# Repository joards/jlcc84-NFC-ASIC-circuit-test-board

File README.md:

# jlcc84-NFC-ASIC-circuit-test-board
PCB created to test custom NFC ASIC in master project.

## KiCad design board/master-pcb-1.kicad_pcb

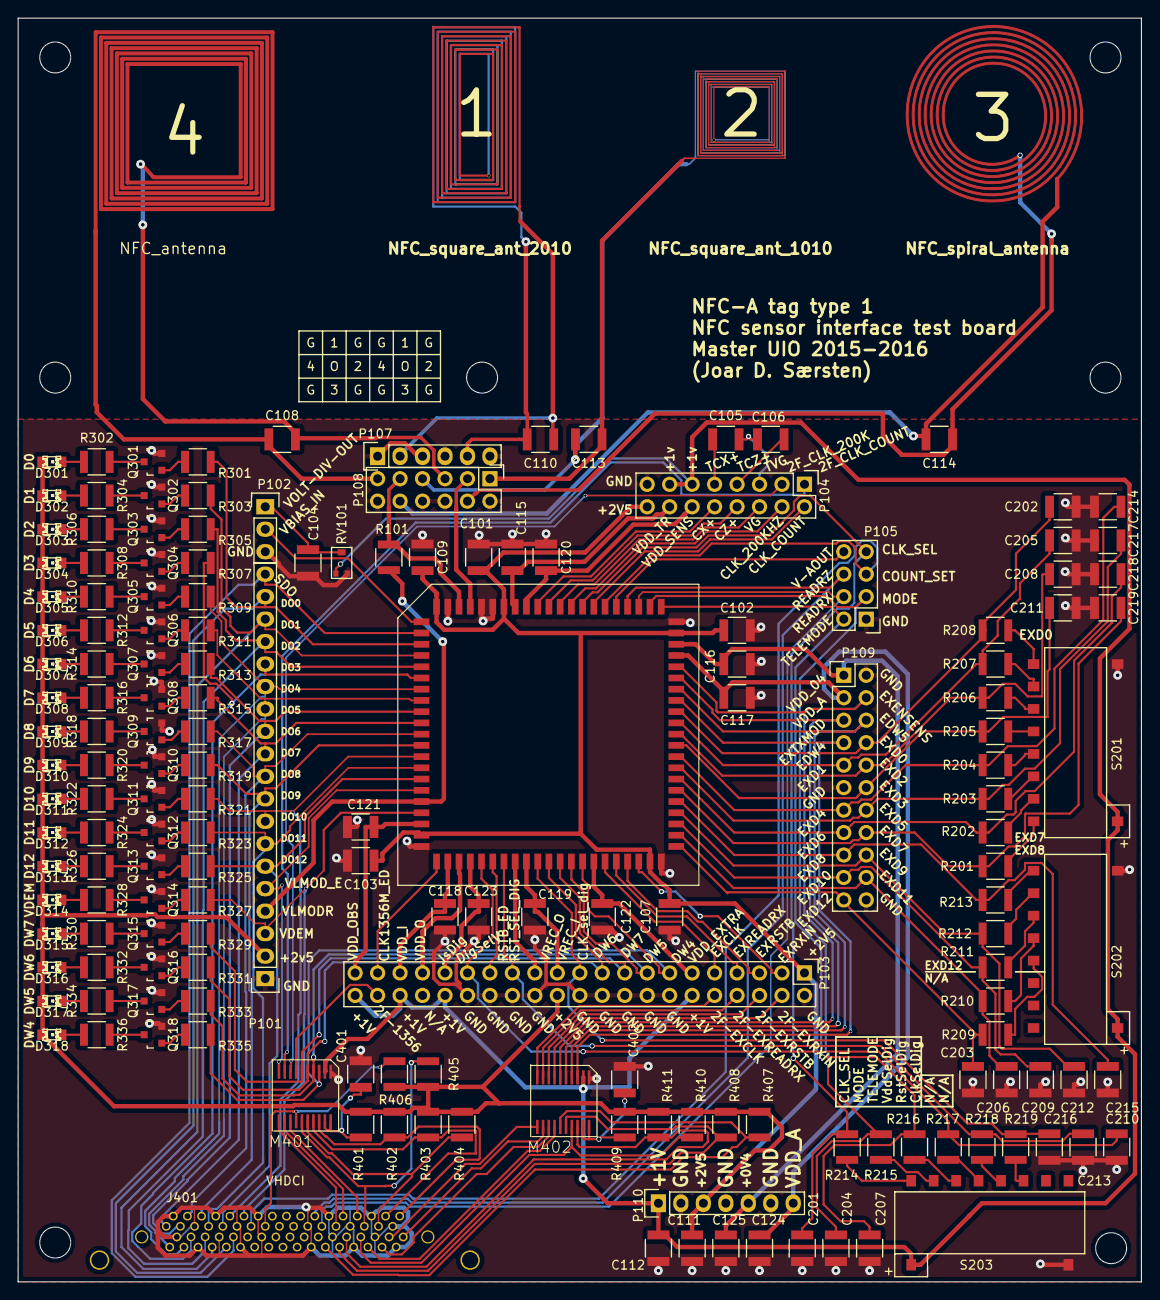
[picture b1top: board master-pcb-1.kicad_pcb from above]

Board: 2 copper layers, 127.0 x 142.9 mm, 177 parts (0 on the bottom side), 186 nets.

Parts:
C101, C102, C103, C104, C107, C109, C116, C117, C201, C202, C203, C204, C205, C206, C207, C208, C209, C210, C211, C212, C213, C214, C215, C216, C217, C218, C219, C401, C402: 100n; C_1210
C105: 4p; C_1210
C106: 3p; C_1210
C108: 45.86p; C_1210
C110, C113, C114: 20p; C_1210
C111, C112, C124, C125: 1u; C_1210
C115, C118, C119, C120, C121, C122, C123: 9n; C_1210
D301, D302, D303, D304, D305, D306, D307, D308, D309, D310, D311, D312, D313, D314, D315, D316, D317, D318: LED; LED-0805
J401: VHDCI
M401, M402: ALI_LSF0108_small; LSF0108
P101: CONN_01X19; Pin_Header_Straight_1x19
P102: CONN_01X03; Pin_Header_Straight_1x03
P103: CONN_02X21; Pin_Header_Straight_2x21
P104: CONN_02X08; Pin_Header_Straight_2x08
P105: CONN_02X04; Pin_Header_Straight_2x04
P106, P111, P112, P113, P114, P115, P116: CONN_01X01; MountingHole_3-5mm
P107: CONN_01X06; Pin_Header_Straight_1x06
P108: CONN_02X06; Pin_Header_Straight_2x06
P109: CONN_02X11; Pin_Header_Straight_2x11
P110: CONN_01X07; Pin_Header_Straight_1x07
Q301, Q302, Q303, Q304, Q305, Q306, Q307, Q308, Q309, Q310, Q311, Q312, Q313, Q314, Q315, Q316, Q317, Q318: BC817-40; SOT-23
R101: R; R_1210
R201, R202, R203, R204, R205, R206, R207, R208, R209, R210, R211, R212, R213, R214, R215, R216, R217, R218, R219: 10k; R_1210
R301, R303, R305, R307, R309, R311, R313, R315, R317, R319, R321, R323, R325, R327, R329, R331, R333, R335: 2k; R_1210
R302, R304, R306, R308, R310, R312, R314, R316, R318, R320, R322, R324, R326, R328, R330, R332, R334, R336: 250; R_1210
R401, R409: 200k; R_1210
R402, R403, R404, R405, R406, R407, R408, R410, R411: 158; R_1210
RV101: 4k7; PVZ2A-pot-smd
S201, S202, S203: DIL-Switch-SPDT; TIMR-08
U101: NFC-SENS-JLCC84; JLCC84
U102: NFC_antenna; NFC_ANT
U103: NFC_square_ant_2010; NFC-ant-square-2010-double
U104: NFC_square_ant_1010; NFC-ant-1010-double
U105: NFC_spiral_antenna; Spiral-NFC-antenna

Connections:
+1V2: C112.1, M401.2, M402.2, P103.12, P103.34, P103.38, P103.42, P104.11, P104.13, P110.1, RV101.1, S201.9, S202.9, S203.9
+2V5: C101.1, C102.1, C103.1, C107.2, C109.2, C111.1, D301.2, D302.2, D303.2, D304.2, D305.2, D306.2, D307.2, D308.2, D309.2, D310.2, D311.2, D312.2, D313.2, D314.2, D315.2, D316.2, D317.2, D318.2, P101.2, P103.1, P103.24, P104.16, P110.3, R401.1, R402.1, R403.1, R404.1, R405.1, R406.1, R407.1, R408.1, R409.1, R410.1, R411.1, U101.10, U101.31, U101.52, U101.68, U101.74
/AZ+: C108.2, P108.5, U102.AC+
/AZ-: C108.1, P108.11, U102.AC-
/CLK1356M_ED: P103.39, U101.12
/CX+: P104.10, U101.65
/CZ+: P104.8, U101.64
/DO0: J401.43, P101.18, R301.2, U101.77
/DO1: J401.41, P101.17, R303.2, U101.78
/DO2: J401.40, P101.16, R305.2, U101.79
/DO3: J401.38, P101.15, R307.2, U101.80
/DO4: J401.37, P101.14, R309.2, U101.81
/DO5: J401.35, P101.13, R311.2, U101.82
/DO6: J401.3, P101.12, R313.2, U101.83
/DO7: J401.1, P101.11, R315.2, U101.84
/DO8: J401.4, P101.10, R317.2, U101.1
/DO9: J401.6, P101.9, R319.2, U101.2
/DO10: J401.10, P101.8, R321.2, U101.3
/DO11: J401.7, P101.7, R323.2, U101.4
/DO12: J401.9, P101.6, R325.2, U101.5
/Diode indicators/DW4: M401.3, P103.13, R335.2, U101.25
/Diode indicators/DW5: M401.4, P103.15, R333.2, U101.24
/Diode indicators/DW6: M401.5, P103.19, R331.2, U101.22
/Diode indicators/DW7: M401.6, P103.17, R329.2, U101.23
/Diode indicators/VDEM: J401.12, P101.3, R327.2, U101.8
/EXD0: C202.2, P109.8, R208.1, U101.45
/EXD1: C205.2, P109.9, R207.1, U101.44
/EXD2: C208.2, P109.10, R206.1, U101.43
/EXD3: C211.2, P109.12, R205.1, U101.42
/EXD4: C214.2, P109.13, R204.1, U101.41
/EXD5: C217.2, P109.14, R203.1, U101.40
/EXD6: C218.2, P109.15, R202.1, U101.39
/EXD7: C219.2, P109.16, R201.1, U101.38
/EXD8: C215.2, P109.17, R213.1, U101.37
/EXD9: C212.2, P109.18, R212.1, U101.36
/EXD10: C209.2, P109.19, R211.1, U101.35
/EXD11: C206.2, P109.20, R210.1, U101.34
/EXD12: C203.2, P109.21, R209.1, U101.33
/FPGA VHDCI connector/2C5_200: J401.28, M401.13
/FPGA VHDCI connector/2C5_COUNT: J401.26, M401.12
/FPGA VHDCI connector/2VLMOD5_E: J401.25, M401.11
/FPGA VHDCI connector/CLK2FPGA: J401.15, M401.14, R406.2
/FPGA VHDCI connector/CLK1356M: M401.7, P103.40
/FPGA VHDCI connector/CLK_200K: M401.8, P104.3
/FPGA VHDCI connector/CLK_COUNT: M401.9, P104.1
/FPGA VHDCI connector/COUNT_SET: J401.13, P105.5, U101.59
/FPGA VHDCI connector/EDW4: M402.3, P109.7, U101.46
/FPGA VHDCI connector/EDW5: M402.4, P109.6, U101.47
/FPGA VHDCI connector/EXCLK: M402.10, P103.10
/FPGA VHDCI connector/EXENSENS: M402.6, P109.4, U101.49
/FPGA VHDCI connector/EXREADRX: M402.9, P103.8
/FPGA VHDCI connector/EXRSTB: M402.8, P103.6
/FPGA VHDCI connector/EXRXIN: M402.7, P103.4
/FPGA VHDCI connector/EXTXMOD: M402.5, P109.5, U101.48
/FPGA VHDCI connector/FECLK: J401.66, M402.11
/FPGA VHDCI connector/FEDW4: J401.60, M402.18, R411.2
/FPGA VHDCI connector/FEDW5: J401.62, M402.17, R410.2
/FPGA VHDCI connector/FERRX: J401.68, M402.12
/FPGA VHDCI connector/HDW4: J401.34, M401.18, R402.2
/FPGA VHDCI connector/HDW5: J401.32, M401.17, R403.2
/FPGA VHDCI connector/HDW6: J401.31, M401.16, R404.2
/FPGA VHDCI connector/HDW7: J401.29, M401.15, R405.2
/FPGA VHDCI connector/READ_RX: J401.23, P105.4, U101.56
/FPGA VHDCI connector/READ_RZ: J401.22, P105.6, U101.57
/FPGA VHDCI connector/SDO: J401.44, P101.19, U101.76
/FPGA VHDCI connector/VLMOD_E: M401.10, P101.5, U101.6
/LS1: C110.1, P107.2, U103.1
/LS2: C110.2, P107.5, U103.2
/RSTB_ED: P103.29, U101.17
/SC1: C113.1, P108.1, U104.1
/SC2: C113.2, P108.7, U104.2
/Selection switches/CLK_SEL: C201.2, P105.7, R214.1, U101.61
/Selection switches/CLK_SEL_DIG: C216.2, P103.21, R219.1, U101.21
/Selection switches/MODE: C204.2, P105.3, R215.1, U101.55
/Selection switches/RST_SEL_DIG: C213.2, P103.27, R218.1, U101.18
/Selection switches/TELEMODE: C207.2, P105.2, R216.1, U101.54
/Selection switches/VDD_SEL_DIG: C210.2, P103.31, R217.1, U101.16
/SpC1: C114.1, P108.4, U105.1
/SpC2: C114.2, P108.10, U105.2
/TCX+: C105.1, P104.9
/TCZ+: C106.1, P104.7
/TVG: C105.2, C106.2, P104.5
/VBIAS_IN: P102.2, U101.75
/VDD_04: C116.1, C125.1, P109.1, P110.5, U101.51
/VDD_A: C117.1, C124.1, P109.3, P110.7, U101.50
/VDD_EXTRA: C122.1, P103.11, U101.26
/VDD_I: C118.1, P103.37, U101.13
/VDD_JS_DIG_ED: C123.1, P103.33, U101.15
/VDD_O: P103.35, U101.14
/VDD_OBS: C121.1, P103.41, U101.9
/VDD_SENS: C120.1, P104.12, U101.66
/VDD_TR: C115.1, P104.14, U101.67
/VG: P104.6, U101.63
/VLMODR: P101.4, R101.2, U101.7
/VREC_I: C119.1, P103.23, U101.20
/VREC_O: P103.25, U101.19
/VRF+: P108.9, R101.1, U101.72
/VRF-: P108.3, U101.71
/V_ANALOG_OUT: P105.8, U101.58
GND: C101.2, C102.2, C103.2, C104.2, C107.1, C109.1, C111.2, C112.2, C115.2, C116.2, C117.2, C118.2, C119.2, C120.2, C121.2, C122.2, C123.2, C124.2, C125.2, C201.1, C202.1, C203.1, C204.1, C205.1, C206.1, C207.1, C208.1, C209.1, C210.1, C211.1, C212.1, C213.1, C214.1, C215.1, C216.1, C217.1, C218.1, C219.1, C401.2, C402.2, J401.2, J401.5, J401.8, J401.11, J401.14, J401.21, J401.24, J401.27, J401.30, J401.33, J401.36, J401.39, J401.42, J401.45, J401.48, J401.55, J401.58, J401.61, J401.64, J401.67, M401.1, M402.1, P101.1, P102.3, P103.2, P103.14, P103.16, P103.18, P103.20, P103.22, P103.26, P103.28, P103.30, P103.32, P104.15, P105.1, P107.1, P107.3, P107.4, P107.6, P108.2, P108.6, P108.8, P108.12, P109.2, P109.11, P109.22, P110.2, P110.4, P110.6, Q301.2, Q302.2, Q303.2, Q304.2, Q305.2, Q306.2, Q307.2, Q308.2, Q309.2, Q310.2, Q311.2, Q312.2, Q313.2, Q314.2, Q315.2, Q316.2, Q317.2, Q318.2, RV101.3, S201.10, S202.10, S203.10, U101.11, U101.32, U101.53, U101.69, U101.70, U101.73
unnamed: C104.1, P102.1, RV101.2
unnamed: C401.1, M401.19, M401.20, R401.2
unnamed: C402.1, M402.19, M402.20, R409.2
unnamed: D301.1, R302.1
unnamed: D302.1, R304.1
unnamed: D303.1, R306.1
unnamed: D304.1, R308.1
unnamed: D305.1, R310.1
unnamed: D306.1, R312.1
unnamed: D307.1, R314.1
unnamed: D308.1, R316.1
unnamed: D309.1, R318.1
unnamed: D310.1, R320.1
unnamed: D311.1, R322.1
unnamed: D312.1, R324.1
unnamed: D313.1, R326.1
unnamed: D314.1, R328.1
unnamed: D315.1, R330.1
unnamed: D316.1, R332.1
unnamed: D317.1, R334.1
unnamed: D318.1, R336.1
unnamed: J401.57, M402.15, R407.2
unnamed: J401.59, M402.16, R408.2
unnamed: J401.63, M402.14
unnamed: J401.65, M402.13
unnamed: P103.3, U101.30
unnamed: P103.5, U101.29
unnamed: P103.7, U101.28
unnamed: P103.9, U101.27
unnamed: P104.2, U101.60
unnamed: P104.4, U101.62
unnamed: Q301.1, R301.1
unnamed: Q301.3, R302.2
unnamed: Q302.1, R303.1
unnamed: Q302.3, R304.2
unnamed: Q303.1, R305.1
unnamed: Q303.3, R306.2
unnamed: Q304.1, R307.1
unnamed: Q304.3, R308.2
unnamed: Q305.1, R309.1
unnamed: Q305.3, R310.2
unnamed: Q306.1, R311.1
unnamed: Q306.3, R312.2
unnamed: Q307.1, R313.1
unnamed: Q307.3, R314.2
unnamed: Q308.1, R315.1
unnamed: Q308.3, R316.2
unnamed: Q309.1, R317.1
unnamed: Q309.3, R318.2
unnamed: Q310.1, R319.1
unnamed: Q310.3, R320.2
unnamed: Q311.1, R321.1
unnamed: Q311.3, R322.2
unnamed: Q312.1, R323.1
unnamed: Q312.3, R324.2
unnamed: Q313.1, R325.1
unnamed: Q313.3, R326.2
unnamed: Q314.1, R327.1
unnamed: Q314.3, R328.2
unnamed: Q315.1, R329.1
unnamed: Q315.3, R330.2
unnamed: Q316.1, R331.1
unnamed: Q316.3, R332.2
unnamed: Q317.1, R333.1
unnamed: Q317.3, R334.2
unnamed: Q318.1, R335.1
unnamed: Q318.3, R336.2
unnamed: R201.2, S201.1
unnamed: R202.2, S201.2
unnamed: R203.2, S201.3
unnamed: R204.2, S201.4
unnamed: R205.2, S201.5
unnamed: R206.2, S201.6
unnamed: R207.2, S201.7
unnamed: R208.2, S201.8
unnamed: R209.2, S202.4
unnamed: R210.2, S202.5
unnamed: R211.2, S202.6
unnamed: R212.2, S202.7
unnamed: R213.2, S202.8
unnamed: R214.2, S203.1
unnamed: R215.2, S203.2
unnamed: R216.2, S203.3
unnamed: R217.2, S203.4
unnamed: R218.2, S203.5
unnamed: R219.2, S203.6

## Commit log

2016-08-03 finalized board and component libraries added
